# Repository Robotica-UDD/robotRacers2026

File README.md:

# RobotRacers

Robot diferencial con PCB RevQ, dos motores Pololu #5178 de 6 V, ruedas de 23 × 40 mm, batería LiPo 2S y control ESP32-S3. Incluye simulación local con cámara cenital, localización AprilTag y corrección por encoders.

## Ejecutar

```sh
./simulation/setup.sh
./simulation/run.command
```

Abre http://127.0.0.1:8000. Iniciar ejecuta A → B → C → D en el laberinto de doble T. La velocidad puede cambiar en marcha; objetivos y tamaño se editan con el robot detenido. Hay vista orbital, cenital y cámara, y ajustes de masa, rozamiento y succión.

Webots R2025a realiza la física y genera las imágenes. Python estima la posición desde esas imágenes y los encoders. El control C++ aplica par a las ruedas; el visor web muestra esa simulación. La posición verdadera solo se utiliza para evaluar errores.

Para cerrar una sesión iniciada en Terminal, pulsa **Ctrl+C** en esa terminal.
Para mostrar también la escena 3D en la ventana de Webots, inicia una sesión con
`./simulation/run.command --visible-webots`. El modo habitual utiliza el visor
web y desactiva la vista local de Webots para ahorrar recursos; por eso esa
ventana puede indicar **No Rendering**, aunque la física y la cámara sigan
activas. El modo visible activa ambas vistas y puede consumir más recursos.

El lanzador cierra sus procesos de Webots y Python. Los registros están en
`simulation/.runtime/`. Si el puerto 8000 está ocupado, cierra la sesión anterior
antes de iniciar otra. Los requisitos de compilación y uso sin conexión se
explican en [Dependencias](docs/dependencias.md).

La validación completó seis misiones en diez minutos sin colisiones. Latencia
imagen → orden aplicada: percentil 95 de 43,64 ms. Cámara: mediana 42,73 imágenes/s;
visor visible: 49,24 fotogramas/s. Los objetivos de 50/60 siguen pendientes de
optimización. Consulta [resultados y límites](docs/validacion-simulacion.md).

El recuadro verde y la línea hacia el objetivo muestran el seguimiento del robot
en las vistas Orbital, Cenital y Cámara. Durante una misión la línea sigue el
objetivo activo; en espera sigue el destino seleccionado. [Cómo funciona el
seguimiento visual](docs/seguimiento-visual.md).

## Probar una webcam real

Para probar una webcam real sin simulador ni ROS 2, ejecuta
`./simulation/webcam/run.command`. Abre un panel independiente en
http://127.0.0.1:8010/ con detección del marcador y orientación del robot.
Consulta [montaje del marcador y prueba de cámara](docs/prueba-webcam.md).

La tarjeta **Robot** permite enlazar la ESP32 por Wi-Fi y ejecutar un único
avance con PWM 100/100 durante 1000 ms. La configuración inicial se envía por
USB desde el mismo panel. [Cómo configurar y probar el control Wi-Fi](docs/prueba-control-wifi.md).

La tarjeta **Navegación** permite calibrar el centro y el frente con dos clics,
marcar varios puntos en la imagen y pulsar **Iniciar recorrido**. Los recorre en
orden y **Borrar puntos** detiene y vacía la lista. La selección nunca
inicia movimiento. Esta prueba usa corrección visual y Wi-Fi, y el firmware
regula velocidades en mm/s con los encoders. La herramienta **Dibujar obstáculo**
permite marcar polígonos de cuatro lados y calcular desvíos con margen para el
robot completo. **Borrar obstáculos** conserva los puntos de destino. La precisión del perfil de movimiento actual
está pendiente de validación física. La corrección durante el avance está filtrada y amortiguada. Una pérdida breve
del marcador conserva el último mando con un presupuesto de tiempo y movimiento cuando no hay obstáculos;
no confirma llegadas sin visión. Ante pérdida prolongada de imagen o Wi-Fi, espera con los motores a cero y
continúa hacia el punto pendiente cuando recupera el seguimiento y la conexión.
D48 y las paradas manuales cancelan el recorrido. Consulta
[navegación con webcam y sus límites](docs/navegacion-webcam.md).

Dos sliders con escala ampliable y entrada numérica ajustan por separado las
máximas de avance y giro, también durante el recorrido. Los valores se guardan y se aplican
con rampas de aceleración y frenado más ágiles; el robot desacelera al acercarse a cada destino.

Para cargar el firmware con arranque por encoders, conecta el robot por USB,
déjalo detenido y ejecuta [`upload_robot.command`](simulation/webcam/upload_robot.command).
El actualizador compila, comprueba el reposo y carga sin borrar la red guardada.

## Referencia física

| Parámetro | Valor | Procedencia |
|---|---|---|
| PCB | RevQ, 130 × 70 × 1,6 mm | Archivos de fabricación |
| Tracción | 2 × Pololu #5178, 6 V, reducción 4,995:1 | Fabricante y montaje |
| Driver | 2 × DRV8874, PH/EN | PCB |
| Ruedas | 23 mm de diámetro, 40 mm de ancho | Ja-Bots |
| Encoder | 59,94 cuentas por vuelta de rueda | 12 × 4,995; ya incluye cuadratura |
| Separación entre centros | 190 mm | Inferida del ancho exterior; ajustable |
| Batería | LiPo 2S, 400 mAh | Usuario |
| Masa inicial | 180 g | Estimación editable |
| Contacto adicional | Patín deslizante | Usuario |
| Sensores laterales | Pololu #4401 de reflectancia | Selección del proyecto |

La dinámica es provisional hasta medir masa, centro de gravedad, fricción y respuesta de motores y turbina. La apariencia se reconstruye desde RevQ; geometrías dimensionales y estimadas se identifican en el manifiesto. La turbina comienza apagada.

## Documentación

- [Comparación de simuladores](docs/comparativa-simuladores.md)
- [Arquitectura y contratos](simulation/CONTRACT.md)
- [Modelos y procedencia](docs/activos_robot.md)
- [Revisión geométrica](docs/activos_revision_geometrica.md)
- [Calibración física](docs/calibracion-fisica.md)
- [ROS 2 y hardware](docs/ros2-y-hardware.md)
- [Validación y rendimiento](docs/validacion-simulacion.md)
- [Navegación física con webcam](docs/navegacion-webcam.md)
- [PCB final](hardware/RevQ)
- [Firmware físico de referencia](firmware/reference)
- [README histórico](docs/historial/README-original.md)

El servicio Python separa cámara, navegación y transporte para incorporar una cámara real y conectar ROS 2 o la ESP32 mediante adaptadores. El simulador no programa el robot físico.

## Licencias

Código del proyecto: MIT. Webots y los modelos mantienen sus propias licencias. La licencia MIT del repositorio no reemplaza las condiciones de los fabricantes.

Los dos sensores laterales y la regleta provisional de 16 canales exponen
reflectancias normalizadas mediante `/api/state`. No participan en la navegación
por cámara de esta entrega. El multiplexor de la regleta no se añade a la PCB
principal.

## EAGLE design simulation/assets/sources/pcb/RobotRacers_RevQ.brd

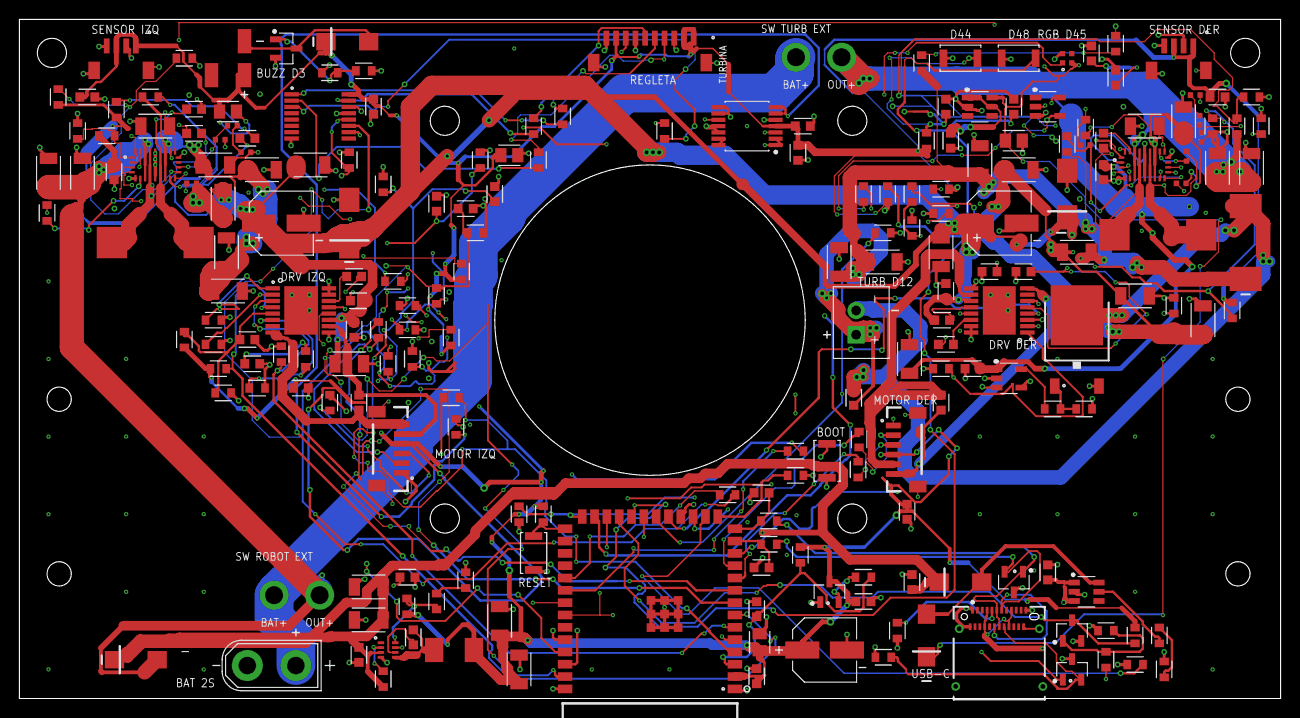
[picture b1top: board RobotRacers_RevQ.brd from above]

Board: 4 copper layers, 130.0 x 70.0 mm, 214 parts (0 on the bottom side), 129 nets.

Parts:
BZ1: MLT-5030; MLT5030
C1: 10uF / 10V X7R; CAPC2012X110
C2, C4: 100nF / 16V X7R; CAPC1608X85
C3: 1uF / 10V X7R; CAPC1608X85
C5, C6: DNP 10pF 50V C0G; CAPC1608X85
C100, C103, C104, C112, C114, C115, C116, C130, C133, C134, C136, C150, C153, C154, C156, C170, C174, C212, C214, C310, C312, C313, C323, C330, C331, C334, C335, C341: 100nF; CAPC1608X85
C101, C102, C105, C106, C110, C111, C113, C117, C118, C119, C120, C121, C132, C152, C171, C172, C173, C210, C211, C213, C217, C218, C219, C220, C221: 22uF/25V; CAPC3216X135
C122, C124, C215, C216, C224: 100nF; CAPC1005_0402
C123, C223: 100pF; CAPC1005_0402
C131, C151: 10nF; CAPC1608X85
C135, C155: 22nF; CAPC1608X85
C222: 22nF; CAPC1005_0402
C311, C333, C336: 10uF; CAPC2012X110
C320, C321, C322: 100pF; CAPC1608X85
C324, C332, C340: 1uF; CAPC1608X85
C350, C351, C352: 100uF/16V; CAPAE660X540N
C353, C354: 22nF/50V; CAPC1608X85
D10: SS1045; SMC_DO214AB
D30: SK6805-EC15; SK6805_EC15
D31, D32, D33, D36: SS14
D34, D35: SMBJ6.5A
J1: 12401832E402A
J10, J11: BM06B-SRSS-TB(LF)(SN); JST-6-SMD-VERT-1.0MM
J12: B2B-XH-A(LF)(SN); JST_XH_B2B_VERTICAL
J20: XT30UPB-M
J30: BM10B-SRSS-TB(LF)(SN); JST_SH_10
J31, J32: BM04B-SRSS-TB(LF)(SN); JST_SH_4
J40, J41: SW_EXTERNO_CABLES; WIRE_SWITCH_2P
L10: 4.7uH/5030; YSPI0530_REVN
L11, L20: 4.7uH/9.5A; IHLP4040DZ_01_4R7
Q1: MMBT3904LT1G; SOT95P237X112-3N
Q10: AOD4184A; TO252
Q30: AO3400A; SOT95P237X112-3N
R1, R2, R3, R4, R10, R12, R103, R123, R124, R125, R143, R144, R145, R326, R327, R328, R330, R331, R334, R341: 10k; RESC1608X60
R5, R127, R128, R129, R147, R148, R149, R320, R321, R322, R323, R324, R325: 1k; RESC1608X60
R6, R7: 5.1k 1%; RESC1608X60
R8, R9, R161, R301, R302: 22R; RESC1608X60
R11, R100, R101, R110, R116, R120, R121, R122, R140, R141, R142, R160, R162, R210, R216, R303, R304, R310, R335: 100k; RESC1608X60
R102: 22k; RESC1608X60
R111, R211: 23.2k; RESC1608X60
R112, R212, R340: 49.9k; RESC1608X60
R113: 12mR/1W; RESC3216X70
R114, R115, R214, R215, R311, R312, R313, R314, R332, R333: 100R; RESC1608X60
R117, R217: 24.9k; RESC1608X60
R118, R218: 3.3k; RESC1005_0402
R126, R146: 2.4k; RESC1608X60
R213: 18mR/1W; RESC3216X70
R300, R360: 4.7k; RESC1608X60
S1: RESET; B3U-1000P(M)
S2: BOOT; B3U-1000P(M)
S3: ACCION_1; B3U-1000P(M)
S4: ACCION_2; B3U-1000P(M)
U1: ESP32-S3-WROOM-1-N16R8; ESP32-S3-WROOM-1
U2: TLV803EA30DBZR; SOT95P237X112-3N
U3, U4: TPD2E2U06QDBZRQ1; SOT95P237X112-3N
U10: TPS62933DRLR; TI_DRL0008A
U11, U20: TPS55289RYQR; TI_RYQ0021A
U12, U13: DRV8874PWPR; TI_PWP0016J
U14: UCC27517DBVR; SOT95P280X145-5N
U31: SN74HC595PWR; TSSOP16_PW
U32: TLV9064IPWR; SOP65P640X120-14
U33: TPS70950DBVR; SOT95P280X145-5N
U34: SN74LV1T34DBVR; SOT95P280X145-5N
U35: TPS2553DBVR; SOT95P280X145-6N

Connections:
3V3_MAIN: BZ1.P, C1.2, C2.2, C4.2, C105.1, C106.1, C136.1, C156.1, C310.1, C311.1, C312.1, C313.1, C323.1, C324.1, C336.1, C350.1, D33.K, J10.4, J11.4, J30.1, J30.2, J30.9, J31.1, J31.3, J32.1, J32.3, L10.2, R1.2, R2.2, R12.2, R101.1, R123.1, R124.1, R143.1, R144.1, R300.1, R330.1, R331.1, R360.1, U1.2, U2.3, U31.16, U32.4
BAR_ANALOG: J30.8, R322.1
BAR_IN: R322.2, U32.10
BAT_RAW: J20.+, J40.2, J41.2
BOOT1_6V: C114.1, U11.20
BOOT2_6V: C115.1, U11.19
BST_3V3: C104.1, U10.6
BUF_BAR: R325.1, U32.8, U32.9
BUF_L: R323.1, U32.1, U32.2
BUF_R: R324.1, U32.6, U32.7
BUF_UNUSED: U32.13, U32.14
BUZZ_GATE: Q30.1, R333.2, R335.1
BUZZ_MINUS: BZ1.N, D33.A, Q30.3
COMP_6V: C123.1, R118.1, U11.15
COMP_RC: C122.1, R118.2
EN_3V3: R100.2, U10.2
EN_6V: R110.2, R111.1, U11.1
ESP_BOOT: R2.1, S2.2, U1.27
ESP_EN: C3.2, R1.1, R5.2, S1.2, U1.3, U31.10
FAN_BAT: C170.1, C171.1, C210.1, C211.1, C212.1, J41.3, R210.1, U14.1, U20.7
FAN_BOOT1_6V: C214.1, U20.20
FAN_BOOT2_6V: C215.1, U20.19
FAN_COMP_6V: C223.1, R218.1, U20.15
FAN_COMP_RC: C222.1, R218.2
FAN_EN_6V: R210.2, R211.1, U20.1
FAN_FB_6V: R216.2, R217.1, U20.14
FAN_FSW_6V: R212.1, U20.6
FAN_GATE: Q10.1, R161.2, R162.1
FAN_GATE_DRV: R161.1, U14.5
FAN_ISN_6V: C216.2, R215.2, U20.13
FAN_ISP_6V: C216.1, R214.2, U20.12
FAN_MINUS: C174.2, D10.2, J12.2, Q10.3
FAN_SW1_6V: C214.2, L20.1, U20.8
FAN_SW2_6V: C215.2, L20.2, U20.10
FAN_VCC_6V: C213.1, U20.18, U20.21
FAN_VM_RAW: C217.1, C218.1, C219.1, C220.1, C224.1, R213.1, R214.1, U20.11
FAN_V_EXT: C172.1, C173.1, C174.1, C221.1, D10.1, J12.1, R213.2, R215.1, R216.1
FB3_LOW: R102.2, R103.1
FB_3V3: R101.2, R102.1, U10.8
FB_6V: R116.2, R117.1, U11.14
FSW_6V: R112.1, U11.6
GND: C1.1, C2.1, C3.1, C4.1, C5.1, C6.1, C100.2, C101.2, C102.2, C103.2, C105.2, C106.2, C110.2, C111.2, C112.2, C113.2, C117.2, C118.2, C119.2, C120.2, C121.2, C122.2, C123.2, C124.2, C130.2, C131.2, C132.2, C133.2, C136.2, C150.2, C151.2, C152.2, C153.2, C156.2, C170.2, C171.2, C172.2, C173.2, C210.2, C211.2, C212.2, C213.2, C217.2, C218.2, C219.2, C220.2, C221.2, C222.2, C223.2, C224.2, C310.2, C311.2, C312.2, C313.2, C320.2, C321.2, C322.2, C323.2, C324.2, C330.2, C331.2, C332.2, C333.2, C334.2, C335.2, C336.2, C340.2, C341.2, C350.2, C351.2, C352.2, D30.4, D34.A, D35.A, J1.A1, J1.A12, J1.B1, J1.B12, J1.SH1, J1.SH2, J1.SH3, J1.SH4, J10.1, J10.P$1, J10.P$2, J11.1, J11.P$1, J11.P$2, J20.-, J30.7, J30.10, J30.MP1, J30.MP2, J31.4, J31.MP1, J31.MP2, J32.4, J32.MP1, J32.MP2, Q1.2, Q10.2, Q30.2, R3.1, R4.1, R6.1, R7.1, R11.1, R103.2, R111.2, R112.2, R117.2, R120.2, R121.2, R122.2, R125.2, R126.2, R140.2, R141.2, R142.2, R145.2, R146.2, R160.2, R162.2, R211.2, R212.2, R217.2, R303.2, R304.2, R310.2, R326.2, R327.2, R328.2, R334.2, R335.2, R341.2, S1.1, S2.1, S3.1, S4.1, U1.1, U1.40, U1.41_1, U1.41_2, U1.41_3, U1.41_4, U1.41_5, U1.41_6, U1.41_7, U1.41_8, U1.41_9, U2.1, U3.3, U4.3, U10.4, U11.5, U11.9, U11.9A, U11.17, U12.9, U12.15, U12.16, U12.17, U13.9, U13.15, U13.16, U13.17, U14.2, U14.4, U20.2, U20.5, U20.9, U20.9A, U20.17, U31.8, U31.13, U32.11, U32.12, U33.2, U34.3, U35.2
GPIO1: C320.1, R323.2, R326.1, U1.39
GPIO2: C321.1, R324.2, R327.1, U1.38
GPIO3_STRAP: R333.1, R334.1, U1.15
GPIO4: C322.1, R325.2, R328.1, U1.4
GPIO5: R121.1, U1.5, U12.2
GPIO6: R122.1, U1.6, U12.3
GPIO7: R123.2, U1.7, U12.4
GPIO8: R140.1, U1.12, U13.1
GPIO9: R141.1, U1.17, U13.2
GPIO10: R142.1, U1.18, U13.3
GPIO11: R143.2, U1.19, U13.4
GPIO12: R160.1, U1.20, U14.3
GPIO13: C131.1, R127.2, U1.21
GPIO14: C151.1, R147.2, U1.22
GPIO15: R128.2, U1.8
GPIO16: R129.2, U1.9
GPIO17: R148.2, U1.10
GPIO18: R149.2, U1.11
GPIO38: R301.1, U1.31
GPIO39: R302.1, U1.32
GPIO40: R360.2, U1.33, U11.3, U20.3
GPIO41: R300.2, U1.34, U11.4, U20.4
GPIO47: R120.1, U1.24, U12.1
GPIO48: C331.1, R331.2, S4.2, U1.25
ISN_6V: C116.2, R115.2, U11.13
ISP_6V: C116.1, R114.2, U11.12
MOTOR_L_CPH: C135.1, U12.13
MOTOR_L_CPL: C135.2, U12.14
MOTOR_L_ENC_A: J10.3, R128.1
MOTOR_L_ENC_B: J10.2, R129.1
MOTOR_L_IPROPI: R126.1, R127.1, U12.6
MOTOR_L_M1: C353.1, J10.6, U12.8
MOTOR_L_M2: C353.2, J10.5, U12.10
MOTOR_L_VCP: C134.1, U12.12
MOTOR_L_VREF: C130.1, R124.2, R125.1, U12.5
MOTOR_R_CPH: C155.1, U13.13
MOTOR_R_CPL: C155.2, U13.14
MOTOR_R_ENC_A: J11.3, R148.1
MOTOR_R_ENC_B: J11.2, R149.1
MOTOR_R_IPROPI: R146.1, R147.1, U13.6
MOTOR_R_M1: C354.1, J11.6, U13.8
MOTOR_R_M2: C354.2, J11.5, U13.10
MOTOR_R_VCP: C154.1, U13.12
MOTOR_R_VREF: C150.1, R144.2, R145.1, U13.5
MUX_S0: R311.1, U31.15
MUX_S0_EXT: J30.6, R311.2
MUX_S1: R312.1, U31.1
MUX_S1_EXT: J30.5, R312.2
MUX_S2: R313.1, U31.2
MUX_S2_EXT: J30.4, R313.2
MUX_S3: R314.1, U31.3
MUX_S3_EXT: J30.3, R314.2
RESET_SUP_N: R5.1, U2.2
RGB_DATA: D30.1, R332.2
RGB_DATA_DRV: R332.1, U34.4
RGB_VDD: C333.1, C334.1, C335.1, D30.2, D36.K, U33.5, U34.5
SIDE_L_ANALOG: J31.2, R320.1
SIDE_L_IN: R320.2, U32.3
SIDE_R_ANALOG: J32.2, R321.1
SIDE_R_IN: R321.2, U32.5
SPI_MOSI: R302.2, R304.1, U31.14
SPI_SCK: R301.2, R303.1, U31.11
SS_3V3: C100.1, U10.7
STRAP_GPIO45: R3.2, U1.26, U34.2
STRAP_GPIO46: R4.2, U1.16
SW1_6V: C114.2, L11.1, U11.8
SW2_6V: C115.2, L11.2, U11.10
SW_3V3: C104.2, L10.1, U10.5
UART0_RX: C330.1, R330.2, S3.2, U1.36
UART0_TX: R310.1, U1.37, U31.12
USB_CC1: J1.A5, R6.2, U4.1
USB_CC2: J1.B5, R7.2, U4.2
USB_DM_CONN: J1.A7, J1.B7, R8.1, U3.2
USB_DM_MCU: C6.2, R8.2, U1.13
USB_DP_CONN: J1.A6, J1.B6, R9.1, U3.1
USB_DP_MCU: C5.2, R9.2, U1.14
USB_ILIM: R340.1, U35.5
USB_ILIM_LOW: R340.2, R341.1
USB_PRESENT_N: Q1.3, R12.1, U1.23
USB_PWR_LIMIT: D31.A, D36.A, U35.6
USB_VBUS: C340.1, J1.A4, J1.A9, J1.B4, J1.B9, R10.1, U35.1, U35.3
VBAT_2S: C110.1, C111.1, C112.1, D32.A, J40.3, R110.1, U11.7
VBUS_BASE: Q1.1, R10.2, R11.2
VCC_6V: C113.1, U11.2, U11.18, U11.21
VIN_LOGIC: C101.1, C102.1, C103.1, C332.1, C341.1, D31.K, D32.K, R100.1, U10.3, U33.1
VM_6V: C121.1, C132.1, C133.1, C134.2, C152.1, C153.1, C154.2, C351.1, C352.1, D34.K, D35.K, R113.2, R115.1, R116.1, U12.11, U13.11
VM_RAW: C117.1, C118.1, C119.1, C120.1, C124.1, R113.1, R114.1, U11.11
